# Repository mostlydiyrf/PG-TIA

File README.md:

# PG-TIA
Programmable-gain termination-insensitive IF amplifier.

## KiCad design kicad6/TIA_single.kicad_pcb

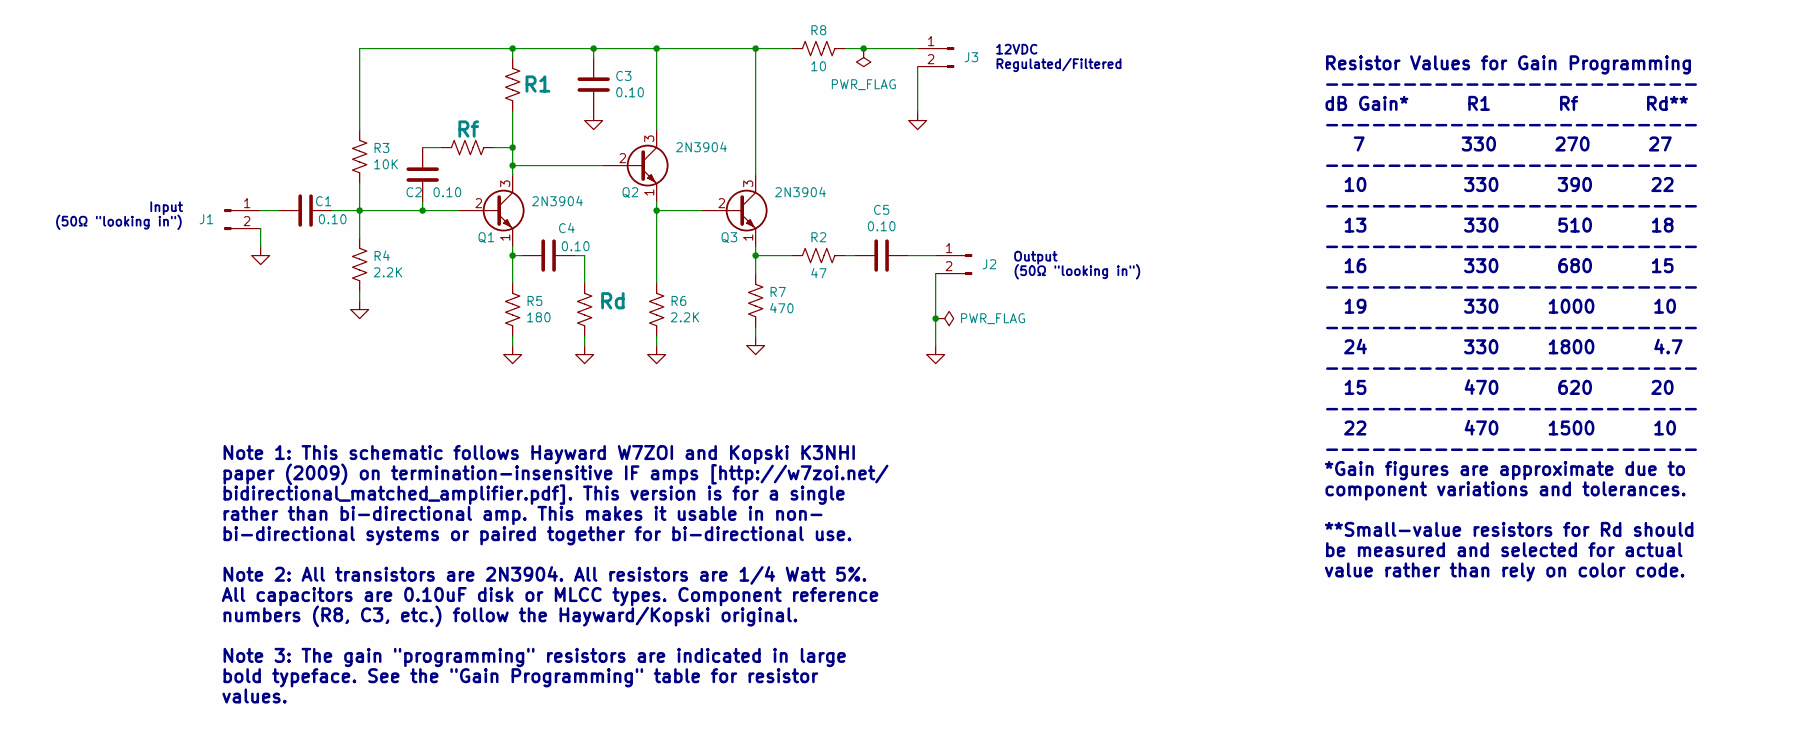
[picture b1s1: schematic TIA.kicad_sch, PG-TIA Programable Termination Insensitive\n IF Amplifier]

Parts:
C1, C2, C3, C4, C5: 0.10; C_Disc_D3.0mm_W1.6mm_P2.50mm
J1, J2: Conn_01x02_Male; SMA_Molex_73251-1153_EdgeMount_Horizontal
J3: Conn_01x02_Male; Molex_KK-254_AE-6410-02A_1x02_P2.54mm_Vertical
Q1, Q2, Q3: 2N3904; TO-92
R1: 330; R_Axial_DIN0204_L3.6mm_D1.6mm_P2.54mm_Vertical
R2: 47; R_Axial_DIN0204_L3.6mm_D1.6mm_P2.54mm_Vertical
R3: 10K; R_Axial_DIN0204_L3.6mm_D1.6mm_P2.54mm_Vertical
R4, R6: 2.2K; R_Axial_DIN0204_L3.6mm_D1.6mm_P2.54mm_Vertical
R5: 180; R_Axial_DIN0204_L3.6mm_D1.6mm_P2.54mm_Vertical
R7: 470; R_Axial_DIN0204_L3.6mm_D1.6mm_P2.54mm_Vertical
R8: 10; R_Axial_DIN0204_L3.6mm_D1.6mm_P2.54mm_Vertical
Rd: 15; R_Axial_DIN0204_L3.6mm_D1.6mm_P2.54mm_Vertical
Rf: 680; R_Axial_DIN0204_L3.6mm_D1.6mm_P2.54mm_Vertical

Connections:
+12V: J3.1, R8.1
GND: C3.1, J1.2, J2.2, J3.2, R4.2, R5.2, R6.2, R7.2, Rd.2
unnamed: C1.1, C2.1, Q1.2 (B), R3.2, R4.1
unnamed: C1.2, J1.1
unnamed: C2.2, Rf.2
unnamed: C3.2, Q2.3 (C), Q3.3 (C), R1.1, R3.1, R8.2
unnamed: C4.1, Rd.1
unnamed: C4.2, Q1.1 (E), R5.1
unnamed: C5.1, J2.1
unnamed: C5.2, R2.1
unnamed: Q1.3 (C), Q2.2 (B), R1.2, Rf.1
unnamed: Q2.1 (E), Q3.2 (B), R6.1
unnamed: Q3.1 (E), R2.2, R7.1

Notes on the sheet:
Note 1: This schematic follows Hayward W7ZOI and Kopski K3NHI paper (2009) on termination-insensitive IF amps [http://w7zoi.net/ bidirectional_matched_amplifier.pdf]. This version is for a single rather than bi-directional amp. This makes it usable in non- bi-directional systems or paired together 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
Output (50Ω "looking in")
Resistor Values for Gain Programming ------------------------ dB Gain* R1 Rf Rd** ------------------------ 7 330 270 27 ------------------------ 10 330 390 22 ------------------------ 13 330 510 18 ------------------------ 16 330 680 15 ------------------------ 19 330 1000 10 ----------------------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
Input (50Ω "looking in")
12VDC Regulated/Filtered

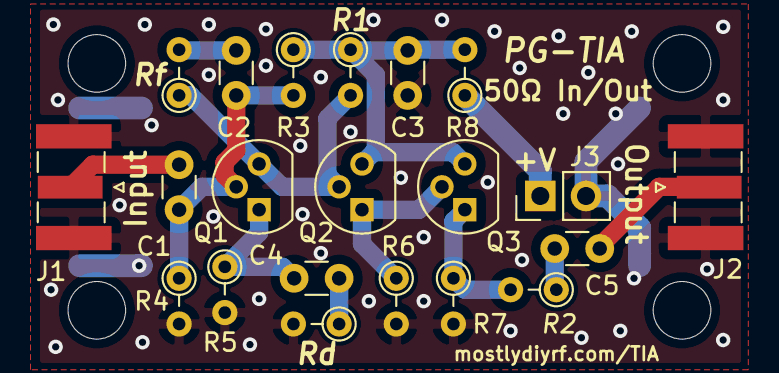
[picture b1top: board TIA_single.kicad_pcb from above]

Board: 2 copper layers, 21 parts (0 on the bottom side), 13 nets.
